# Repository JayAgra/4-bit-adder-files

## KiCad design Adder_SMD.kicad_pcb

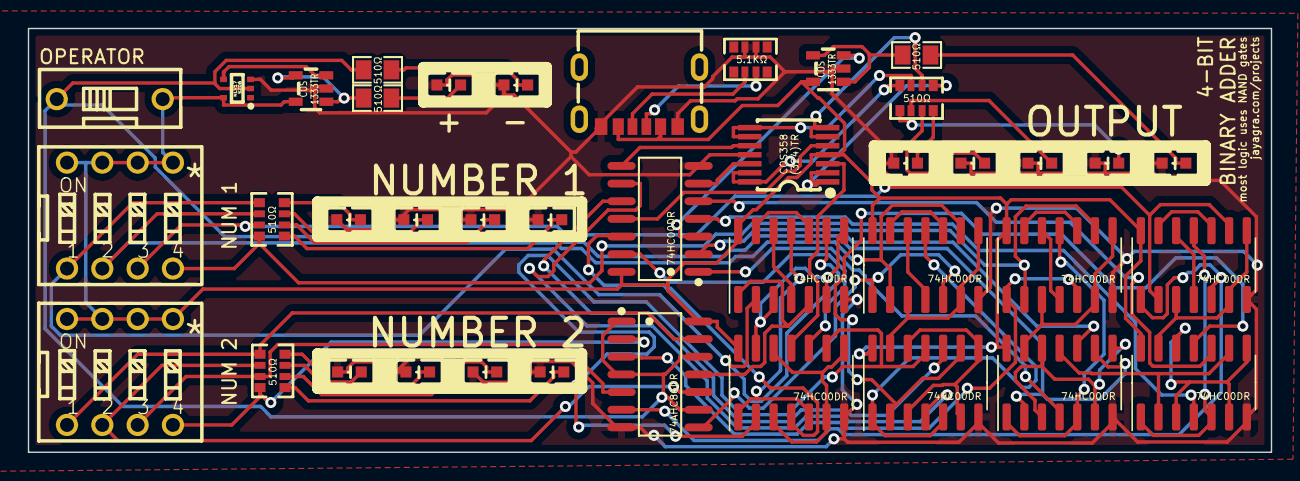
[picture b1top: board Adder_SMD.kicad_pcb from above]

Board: 2 copper layers, 89.4 x 30.5 mm, 40 parts (0 on the bottom side), 75 nets.

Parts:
LED1, LED2, LED3, LED4, LED5, LED6, LED7, LED8, LED9, LED10, LED11, LED12, LED13, LED14, LED15: 19-217_R6C-AL1M2VY_3T; LED0603-R-RD
NUM 1, NUM 2: VDG_S-04HG-R; SW-TH_8P-L11.7-W9.9-P2.54
OPERATOR: DSWB01LHGET; SW-TH_DSWB01LHGET
R2, R4, R5: RC0805JR-07510RL; R0805
RN1, RN3, RN4: 4D03WGJ0511T5E; RES-ARRAY-SMD_0603-8P-L3.2-W1.6-BL
RN5: CN1J4TTD512J; RES-ARRAY-SMD_0603-8P-L3.2-W1.6-BL
U1: COS358(324)TR; TSSOP-14_L5.0-W4.4-P0.65-LS6.4-BL
U2: SN74AHC86DR; SOIC-14_L8.7-W3.9-P1.27-LS6.0-BL
U3, U6: COS1333TR; SOT-23-5_L2.9-W1.6-P0.95-LS2.8-BL
U4: NLV17SZ06DFT2G; SC-88A_L2.0-W1.3-P0.65-LS2.1-BR
U5: SN74HC00DR; SOIC-14_L8.7-W3.9-P1.27-LS6.0-BL
U7, U8, U9, U10, U11, U12, U13, U14: 4011; SOIC-14_3.9x8.7mm_P1.27mm
USB1: U262-061N-4BVC11; USB-SMD_U262-061N-4BVC11

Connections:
+5V: NUM 1.5, NUM 1.6, NUM 1.7, NUM 1.8, NUM 2.5, NUM 2.6, NUM 2.7, NUM 2.8, OPERATOR.2, U1.4 (+VS), U2.14 (VCC), U3.5 (+VS), U4.5 (VCC), U5.14 (VCC), U6.5 (+VS), U7.14 (VDD), U8.14 (VDD), U9.14 (VDD), U10.14 (VDD), U11.14 (VDD), U12.14 (VDD), U13.14 (VDD), U14.14 (VDD), USB1.A9 (VBUS), USB1.B9 (VBUS)
/full_adder1/A: NUM 1.2, RN1.2, U9.2, U9.9
/full_adder1/CIN: U10.2, U10.9, U12.11
/full_adder2/A: NUM 1.3, RN1.3, U11.2, U11.9
/full_adder2/CIN: U12.2, U12.9, U14.11
/full_adder3/A: NUM 1.4, RN1.4, U13.2, U13.9
/full_adder/A: NUM 1.1, RN1.1, U7.2, U7.9
/full_adder/CIN: U8.2, U8.9, U10.11
/full_adder/COUT: U1.3 (INA+), U8.11
GND: LED1.2 (C), LED2.2 (C), LED3.2 (C), LED4.2 (C), LED5.2 (C), LED6.2 (C), LED7.2 (C), LED8.2 (C), LED9.2 (C), LED10.2 (C), LED11.2 (C), LED12.2 (C), LED13.2 (C), LED14.2 (C), LED15.2 (C), RN5.6, RN5.7, U1.11 (-VS), U2.7 (GND), U3.2 (-VS), U4.3 (GND), U5.7 (GND), U6.2 (-VS), U7.7 (VSS), U8.7 (VSS), U9.7 (VSS), U10.7 (VSS), U11.7 (VSS), U12.7 (VSS), U13.7 (VSS), U14.7 (VSS), USB1.A12 (GND), USB1.B12 (GND)
NAND1A: U5.1 (1A), U14.4
NAND1B: U5.2 (1B), U14.10
NAND1Y: U3.3 (+IN), U5.3 (1Y)
NAND2A: U5.4 (2A), U12.4
NAND2B: U5.5 (2B), U12.10
NAND2Y: U1.12 (+IND), U5.6 (2Y)
NAND3A: U5.9 (3A), U10.4
NAND3B: U5.10 (3B), U10.10
NAND3Y: U1.10 (+INC), U5.8 (3Y)
NAND4A: U5.12 (4A), U8.4
NAND4B: U5.13 (4B), U8.10
NAND4Y: U1.5 (+INB), U5.11 (4Y)
unnamed: LED1.1 (A), RN1.8
unnamed: LED2.1 (A), RN1.7
unnamed: LED3.1 (A), RN1.6
unnamed: LED4.1 (A), RN1.5
unnamed: LED5.1 (A), RN3.8
unnamed: LED6.1 (A), RN4.8
unnamed: LED7.1 (A), RN3.7
unnamed: LED8.1 (A), RN4.7
unnamed: LED9.1 (A), RN3.6
unnamed: LED10.1 (A), RN4.6
unnamed: LED11.1 (A), RN3.5
unnamed: LED12.1 (A), RN4.5
unnamed: LED13.1 (A), R2.2
unnamed: LED14.1 (A), R4.2
unnamed: LED15.1 (A), R5.2
unnamed: R4.1, U3.1 (OUT), U3.4 (-IN)
unnamed: R5.1, U6.1 (OUT), U6.4 (-IN)
unnamed: RN3.1, U1.1 (OUTA), U1.2 (INA-)
unnamed: RN3.2, U1.6 (-INB), U1.7 (OUTB)
unnamed: RN3.3, U1.8 (OUTC), U1.9 (-INC)
unnamed: RN3.4, U1.13 (-IND), U1.14 (OUTD)
unnamed: RN5.2, USB1.B5 (CC2)
unnamed: RN5.3, USB1.A5 (CC1)
unnamed: U4.4 (~OUTY), U6.3 (+IN)
unnamed: U7.3, U7.6, U7.8, U8.13
unnamed: U7.10, U7.13
unnamed: U7.11, U8.1, U8.5
unnamed: U7.4, U7.12
unnamed: U8.3, U8.6, U8.8, U8.12
unnamed: U9.10, U9.13
unnamed: U9.4, U9.12
unnamed: U9.11, U10.1, U10.5
unnamed: U10.3, U10.6, U10.8, U10.12
unnamed: U9.3, U9.6, U9.8, U10.13
unnamed: U11.3, U11.6, U11.8, U12.13
unnamed: U11.10, U11.13
unnamed: U11.11, U12.1, U12.5
unnamed: U11.4, U11.12
unnamed: U12.3, U12.6, U12.8, U12.12
unnamed: U13.3, U13.6, U13.8, U14.13
unnamed: U13.10, U13.13
unnamed: U13.11, U14.1, U14.5
unnamed: U13.4, U13.12
unnamed: U14.3, U14.6, U14.8, U14.12
XOR1A: OPERATOR.1 (A1), R2.1, U2.1 (1A), U2.4 (2A), U2.9 (3A), U2.12 (4A), U4.2 (INA), U14.2, U14.9
XOR1B: NUM 2.4, RN4.4, U2.2 (1B)
XOR1Y: U2.3 (1Y), U13.1, U13.5
XOR2B: NUM 2.3, RN4.3, U2.5 (2B)
XOR2Y: U2.6 (2Y), U11.1, U11.5
XOR3B: NUM 2.2, RN4.2, U2.10 (3B)
XOR3Y: U2.8 (3Y), U9.1, U9.5
XOR4B: NUM 2.1, RN4.1, U2.13 (4B)
XOR4Y: U2.11 (4Y), U7.1, U7.5
